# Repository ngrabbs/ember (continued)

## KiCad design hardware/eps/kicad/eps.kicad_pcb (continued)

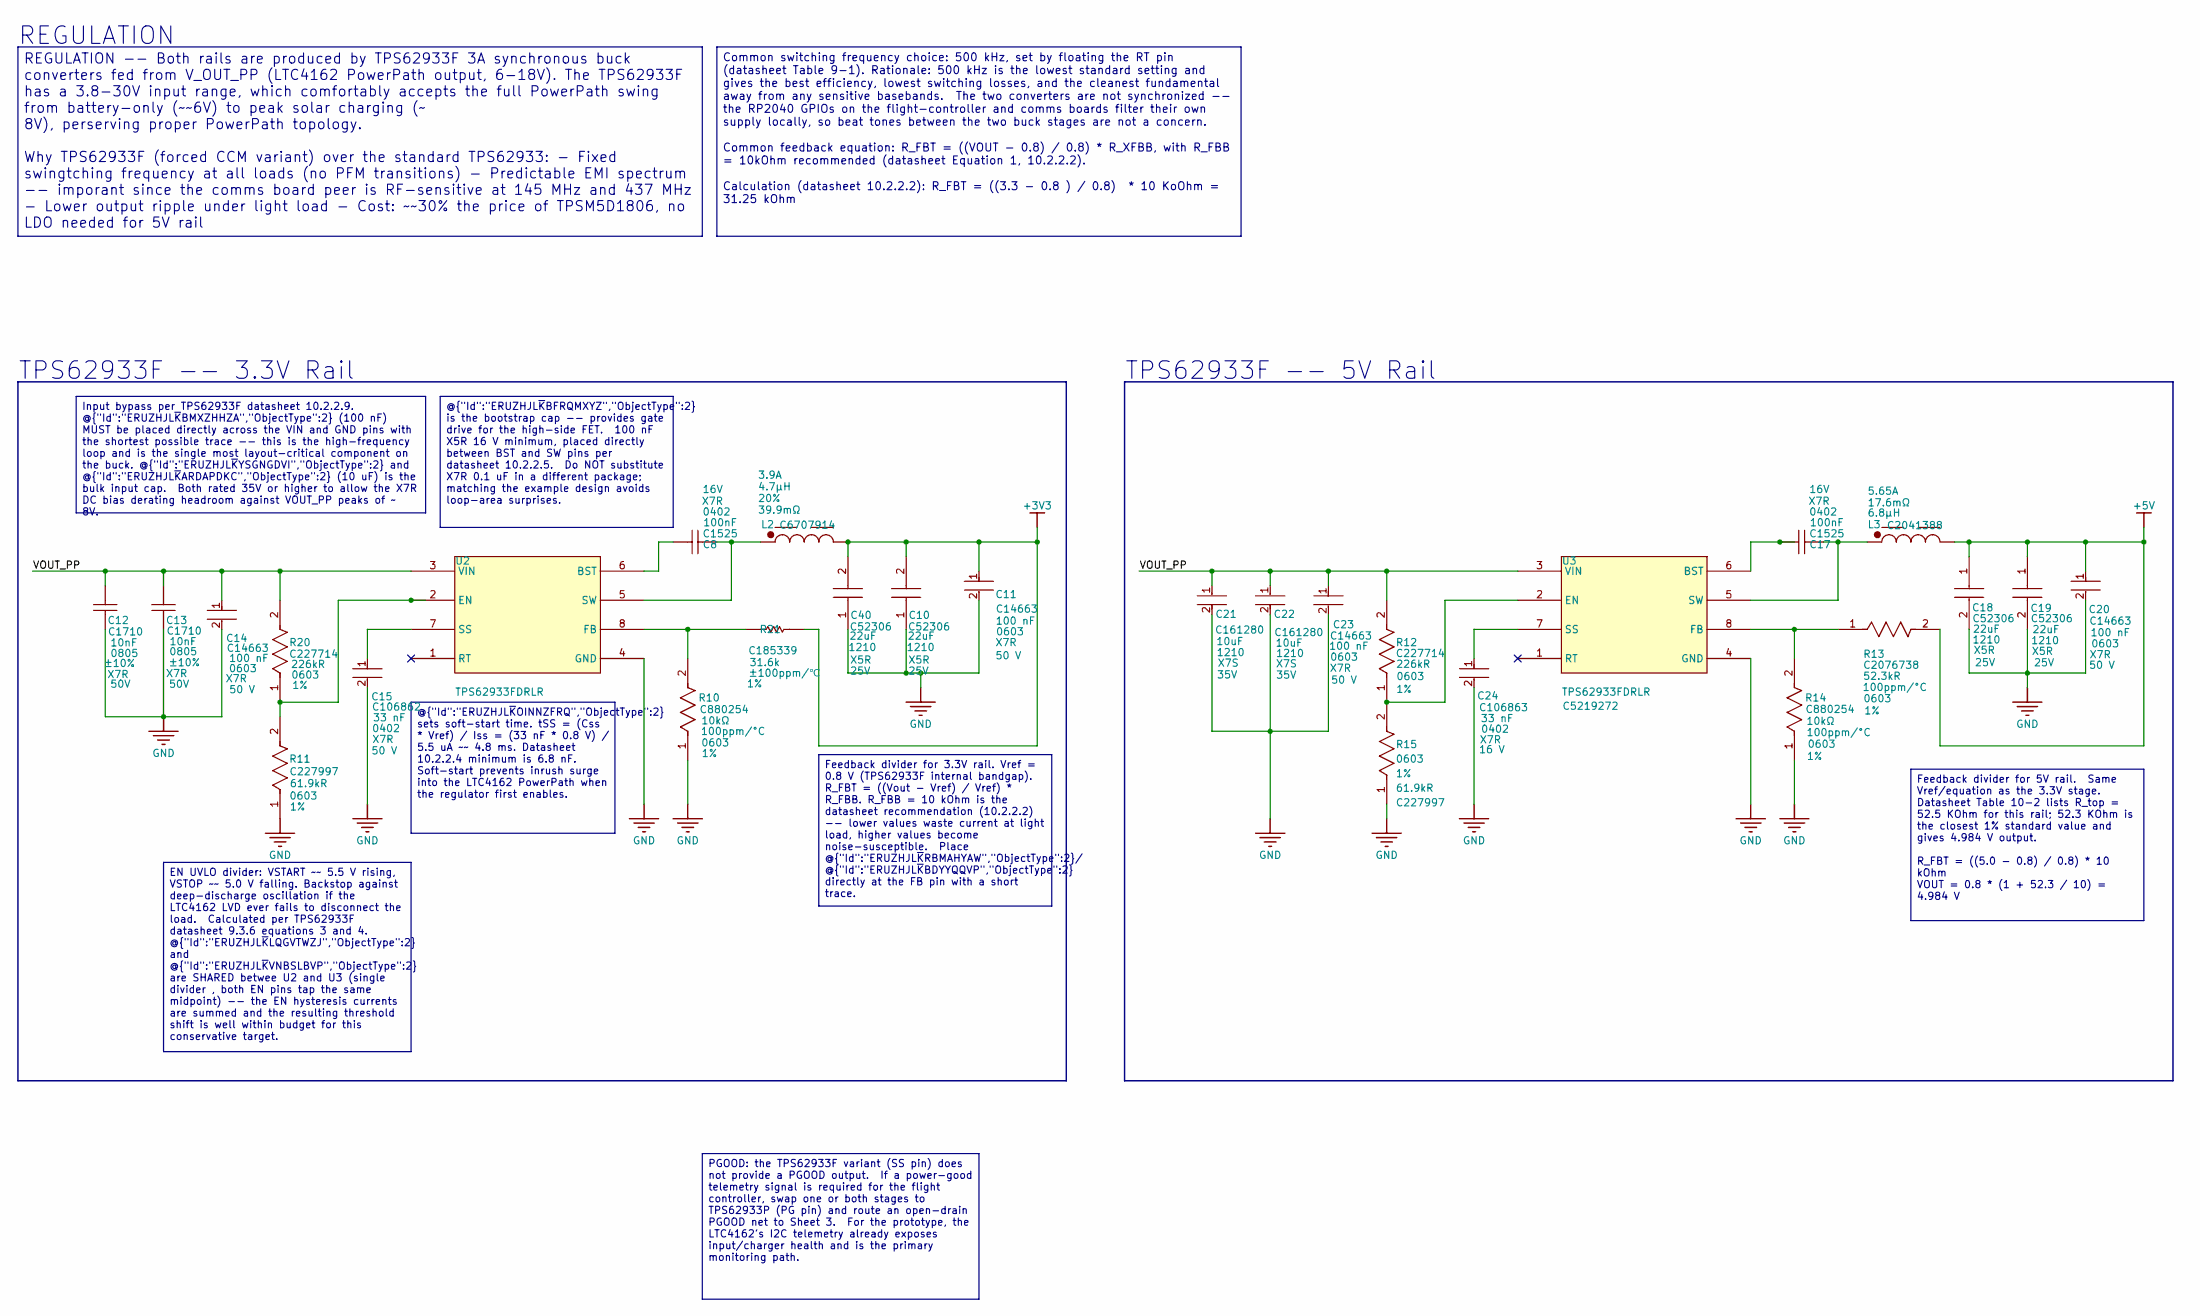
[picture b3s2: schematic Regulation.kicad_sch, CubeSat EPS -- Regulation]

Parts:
C8, C17: CL05B104KO5NNNC; CAPC1050X55X23ML05T13; TOLERANCE (%) ±10%; RATED VOLTAGE 16V; LCSC PART # C1525
C10, C18, C19, C40: CL32A226KAJNNNE; CAPC3225X270N; VOLTAGE 25V; MANUFACTURER_PART_NUMBER CL32A226KAJNNNE; MOUSER PART NUMBER 187-CL32A226KAJNNNE
C11, C14, C20, C23: C14663; FP-CC0603-DA-MFG; VOLTAGE 50 V; VOLTAGE RATING 50 V; MANUFACTURER PART NUMBER CC0603KRX7R9BB104; MOUSER DESCRIPTION Multilayer Ceramic Capacitor, CC Series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
C12, C13: CL21B103KBANNNC; CAPC2013X75X45LL10T25; TOLERANCE (%) ±10%; RATED VOLTAGE 50V; LCSC PART # C1710
C15: CC0402KRX7R9BB333; FP-CC0402-MFG; VOLTAGE RATING 50 V; TOLERANCE 0.1; MANUFACTURER PART NUMBER CC0402KRX7R9BB333; MOUSER DESCRIPTION Cap Ceramic 0.033uF 50VDC X7R 10% SMD 0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
C21, C22: GCM32EC7YA106KA03L; FP-GCM32E-0_3-IPC_B; VOLTAGE RATING (DC) 35V; RATINGS AEC-Q200; LCSC PART # C161280
C24: CC0402KRX7R7BB333; FP-CC0402-MFG; VOLTAGE RATING 16 V; TOLERANCE 0.1; MANUFACTURER PART NUMBER CC0402KRX7R7BB333; DIGIKEY DESCRIPTION CAP CER 0.033UF 16V X7R 0402
L2: 74438357047; WE-MAPI_4030; INDUCTANCE TOLERANCE 20%; CURRENT RATING 3.9A; LCSC PART # C6707914
L3: 74439346068; WE-XHMI_6060; CURRENT RATING 6.5A; INDUCTANCE TOLERANCE 20%; LCSC PART # C2041388
R10, R14: SG73P1JTTD1002F; FP-SG73P1J-MFG; POWER RATING 200mW; VOLTAGE RATING (DC) 50V; LCSC PART # C880254
R11, R15: AC0603FR-0761K9L; FP-AC0603-IPC_C; POWER RATING 100mW; TOLERANCE 1%; LCSC PART # C227997
R12, R20: AC0603FR-07226KL; FP-AC0603-IPC_B; POWER RATING 100mW; VOLTAGE RATING 50V; LCSC PART # C227714
R13: CRCW060352K3FKEA; FP-CRCW0603-e3-IPC_B; VOLTAGE RATING 75V; TOLERANCE 1%; LCSC PART # C2076738
R21: RC0603FR-0731K6L; RESC1608X55X25NL10T15; TOLERANCE 1%; PART NUMBER RC0603FR-0731K6L; LCSC PART # C185339
U2: TPS62933FDRLR; SOT5X3-8_DRL_TEX; MANUFACTURER_PART_NUMBER TPS62933FDRLR
U3: TPS62933FDRLR; SOT5X3-8_DRL_TEX; MANUFACTURER_PART_NUMBER TPS62933FDRLR; LCSC PART # C5219272

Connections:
+3V3: C10.2, C11.1, C40.2, L2.2, R21.2; also elsewhere on the board
+5V: C18.1, C19.1, C20.1, L3.2, R13.2; also elsewhere on the board
/Regulation/VOUT_PP: C12.1, C13.1, C14.1, C21.1, C22.1, C23.1, R12.2, R20.2, U2.3 (VIN), U3.3 (VIN)
GND: C10.1, C11.2, C12.2, C13.2, C14.2, C15.2, C18.2, C19.2, C20.2, C21.2, C22.2, C23.2, C24.2, C40.1, R10.1, R11.1, R14.1, R15.1, U2.4 (GND), U3.4 (GND); also elsewhere on the board
unnamed: C8.1, U2.6 (BST)
unnamed: R11.2, R20.1, U2.2 (EN)
unnamed: R10.2, R21.1, U2.8 (FB)
unnamed: C15.1, U2.7 (SS)
unnamed: C8.2, L2.1, U2.5 (SW)
unnamed: C17.1, U3.6 (BST)
unnamed: R12.1, R15.2, U3.2 (EN)
unnamed: R13.1, R14.2, U3.8 (FB)
unnamed: C24.1, U3.7 (SS)
unnamed: C17.2, L3.1, U3.5 (SW)

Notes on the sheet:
REGULATION
TPS62933F -- 5V Rail
TPS62933F -- 3.3V Rail
Feedback divider for 3.3V rail. Vref = 0.8 V (TPS62933F internal bandgap). R_FBT = ((Vout - Vref) / Vref) * R_FBB. R_FBB = 10 kOhm is the datasheet recommendation (10.2.2.2) -- lower values waste current at light load, higher values become noise-susceptible. Place @{"Id":"ERUZHJL~{K}RBMAHYAW","Obje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
Input bypass per TPS62933F datasheet 10.2.2.9. @{"Id":"ERUZHJL~{K}BMXZHHZA","ObjectType":2} (100 nF) MUST be placed directly across the VIN and GND pins with the shortest possible trace -- this is the high-frequency loop and is the single most layout-critical component on the buck. @{"Id":"ERUZHJL~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
@{"Id":"ERUZHJL~{K}BFRQMXYZ","ObjectType":2} is the bootstrap cap -- provides gate drive for the high-side FET. 100 nF X5R 16 V minimum, placed directly between BST and SW pins per datasheet 10.2.2.5. Do NOT substitute X7R 0.1 uF in a different package; matching the example design avoids loop-area 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
@{"Id":"ERUZHJL~{K}OINNZFRQ","ObjectType":2} sets soft-start time. tSS = (Css * Vref) / Iss = (33 nF * 0.8 V) / 5.5 uA ~~ 4.8 ms. Datasheet 10.2.2.4 minimum is 6.8 nF. Soft-start prevents inrush surge into the LTC4162 PowerPath when the regulator first enables.
EN UVLO divider: VSTART ~~ 5.5 V rising, VSTOP ~~ 5.0 V falling. Backstop against deep-discharge oscillation if the LTC4162 LVD ever fails to disconnect the load. Calculated per TPS62933F datasheet 9.3.6 equations 3 and 4. @{"Id":"ERUZHJL~{K}LQGVTWZJ","ObjectType":2} and @{"Id":"ERUZHJL~{K}VNBSLBVP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
Feedback divider for 5V rail. Same Vref/equation as the 3.3V stage. Datasheet Table 10-2 lists R_top = 52.5 KOhm for this rail; 52.3 KOhm is the closest 1% standard value and gives 4.984 V output. R_FBT = ((5.0 - 0.8) / 0.8) * 10 kOhm VOUT = 0.8 * (1 + 52.3 / 10) = 4.984 V
REGULATION -- Both rails are produced by TPS62933F 3A synchronous buck converters fed from V_OUT_PP (LTC4162 PowerPath output, 6-18V). The TPS62933F has a 3.8-30V input range, which comfortably accepts the full PowerPath swing from battery-only (~~6V) to peak solar charging (~ 8V), perserving prope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
PGOOD: the TPS62933F variant (SS pin) does not provide a PGOOD output. If a power-good telemetry signal is required for the flight controller, swap one or both stages to TPS62933P (PG pin) and route an open-drain PGOOD net to Sheet 3. For the prototype, the LTC4162's I2C telemetry already exposes i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
Common switching frequency choice: 500 kHz, set by floating the RT pin (datasheet Table 9-1). Rationale: 500 kHz is the lowest standard setting and gives the best efficiency, lowest switching losses, and the cleanest fundamental away from any sensitive basebands. The two converters are not synchron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

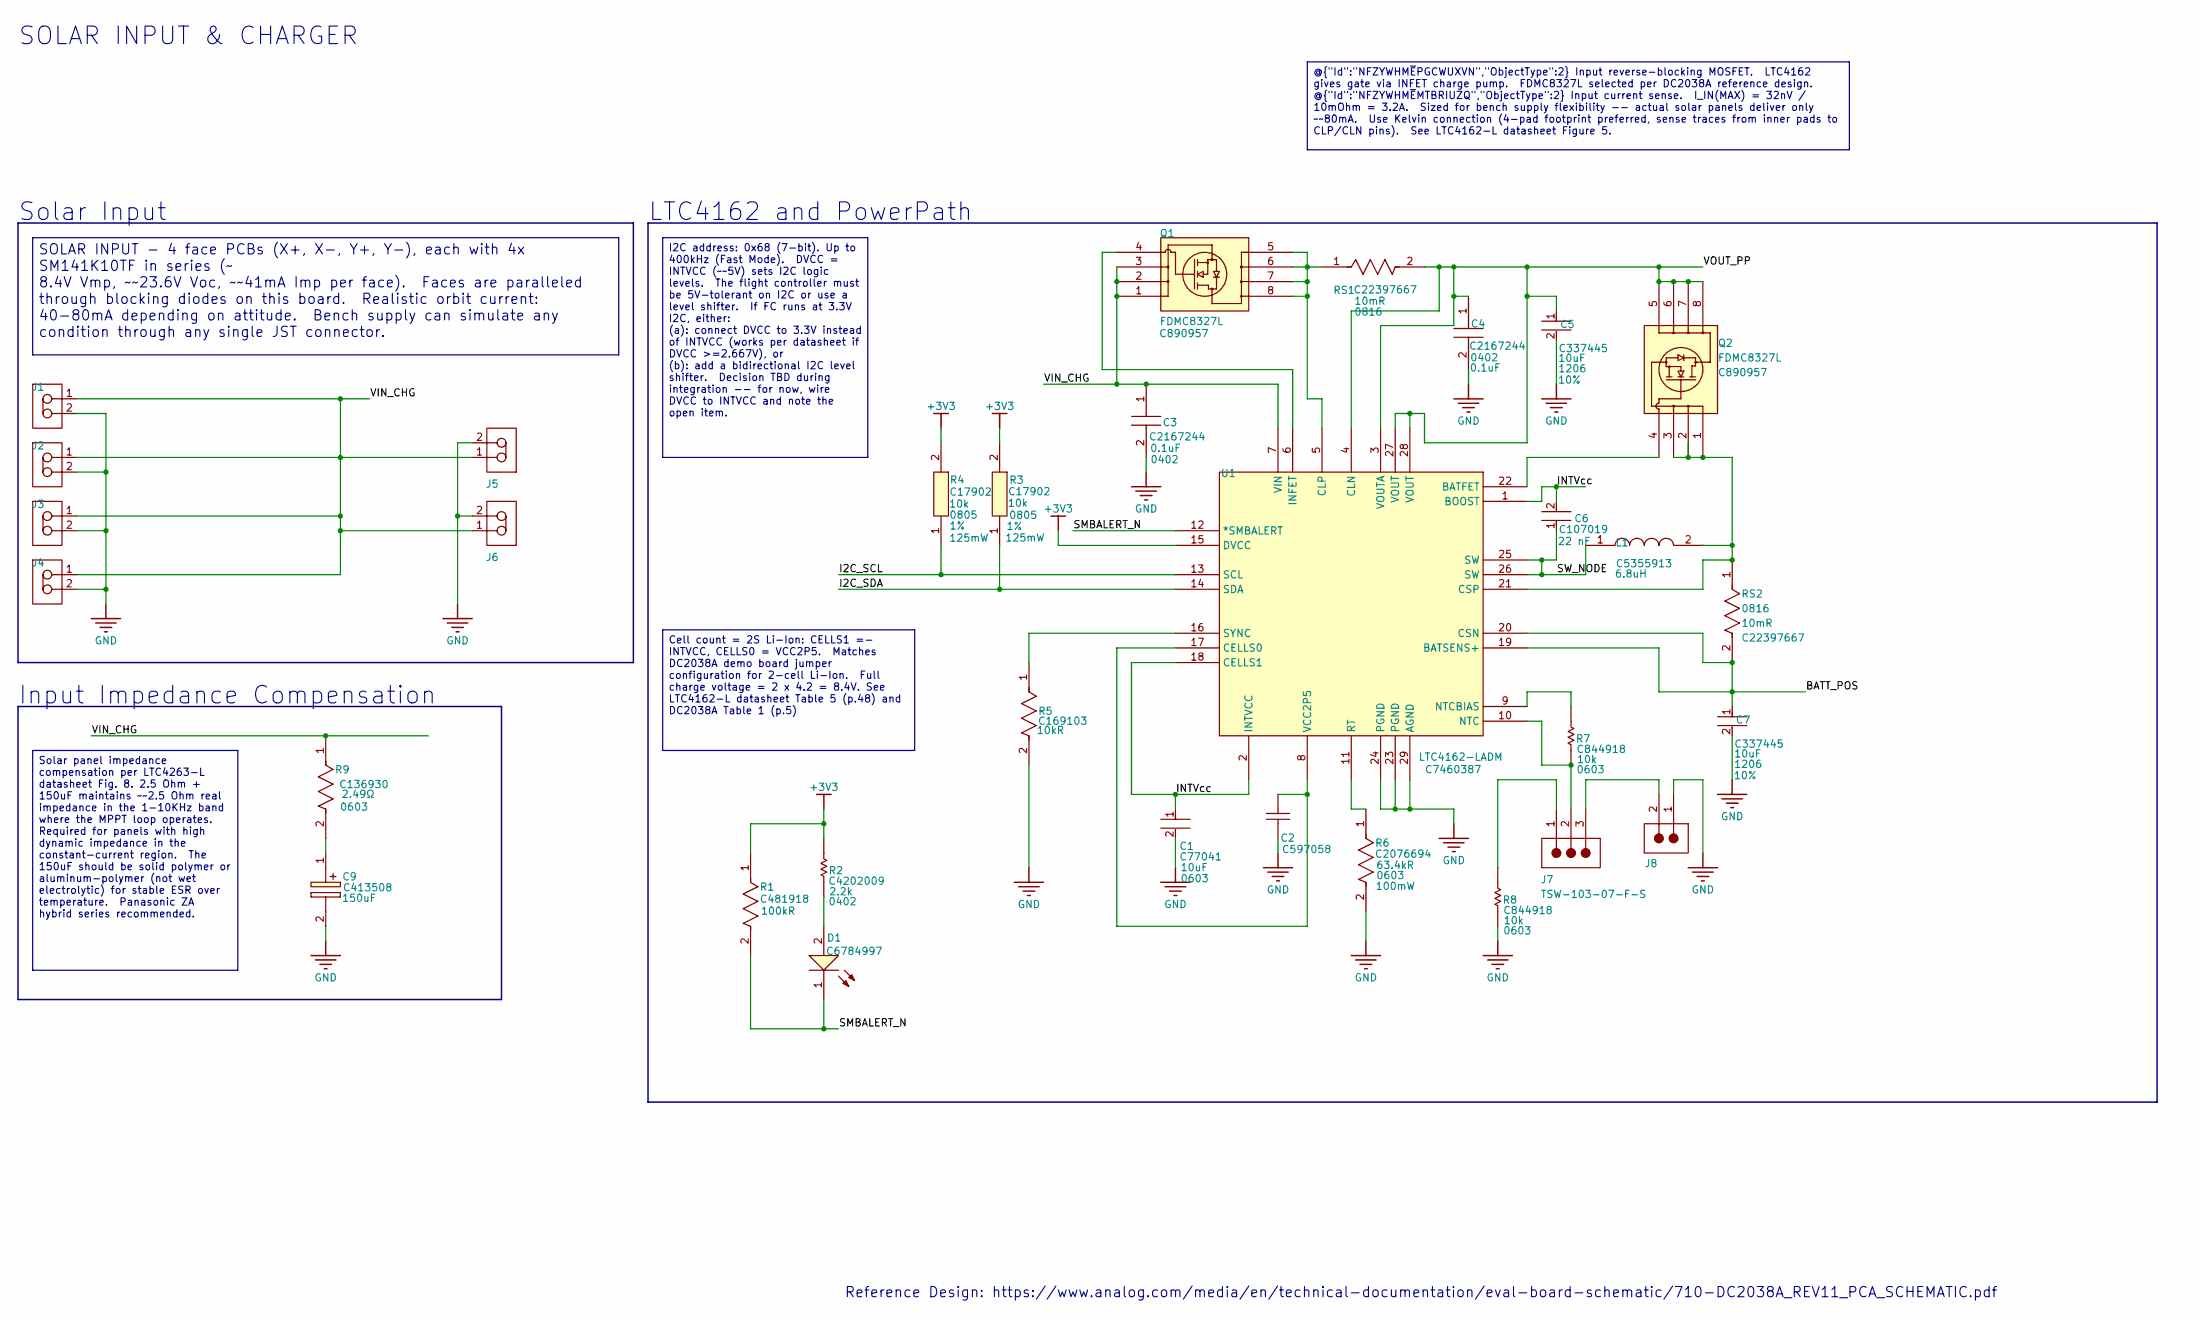
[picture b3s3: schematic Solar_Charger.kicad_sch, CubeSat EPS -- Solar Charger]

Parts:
C1: GRM188R60J106ME47D; FP-GRM188-0_1-e0_2_0_55-IPC_A; VOLTAGE RATING (DC) 6.3V; VOLTAGE RATING 6.3V; LCSC PART # C77041
C2: 0402YD105KAT2A; CAPC1005X56X25ML10T15; PART NUMBER 0402YD105KAT2A; LCSC PART # C597058
C3, C4: 04025C104KAT2A; CAPC1005X56N; MANUFACTURER_PART_NUMBER 04025C104KAT2A; MOUSER PART NUMBER 581-04025C104KAT2A
C5, C7: UMK316BBJ106KL-T; FP-1206-L_3_2_0_3-W_1_6_0-IPC_A; VOLTAGE RATING 50V; TOLERANCE 10%; LCSC PART # C337445
C6: CC0402KRX7R8BB223; FP-CC0402-MFG; VOLTAGE RATING 25 V; TOLERANCE 0.1; MANUFACTURER PART NUMBER CC0402KRX7R8BB223; DIGIKEY DESCRIPTION CAP CER 0.022UF 25V X7R 0402
C9: EEEFK1H151P; EEE0JA152UAP; MANUFACTURER_PART_NUMBER EEEFK1H151P; LCSC PART # C413508
D1: 150060YS75000; WL-SMCW_0603_150060xx75000; REVERSE VOLTAGE 5V; FORWARD VOLTAGE 2V; LCSC PART # C6784997
J1, J2, J3, J4, J5, J6: B2B-PH-K-S(LF)(SN); JST-B2B-PH-K-S_V
J7: TSW-103-07-F-S; SMTC-TSW-103-07-X-S; PARTNUMBER TSW-103-07-F-S
J8: 68000-102HLF; AMPH-68000-102HLF_V; VOLTAGE RATING 1.5kV; FLAMMABILITY RATING UL94V-0
L1: XAL6060-682MEC; XAL6060682MEC; MANUFACTURER_PART_NUMBER XAL6060-682MEC; MOUSER PART NUMBER 994-XAL6060-682MEC
Q1, Q2: FDMC8327L; WDFN8_511DR_OSI; MANUFACTURER_PART_NUMBER FDMC8327L; LCSC PART # C890957
R1: CRCW0402100KFKED; FP-CRCW0402-e3-IPC_C; POWER RATING 63mW; VOLTAGE RATING (DC) 50V; LCSC PART # C481918
R2: CRCW04022K20JNED; RESC1005X40X25NL05T05; PART NUMBER CRCW04022K20JNED; LCSC PART # C4202009
R3, R4: 1206W4F1002T5E; RESC3116X65N; TOLERANCE 1%; MANUFACTURER_PART_NUMBER 1206W4F1002T5E; LCSC PART # C17902
R5: CRCW060310K0JNEA; FP-CRCW0603-e3-MFG; TOLERANCE 5%; VOLTAGE RATING 75V; LCSC PART # C169103
R6: CRCW060363K4FKEA; FP-CRCW0603-e3-IPC_B; VOLTAGE RATING (DC) 75V; VOLTAGE RATING 75V; LCSC PART # C2076694
R7, R8: CRCW060310K0FKEA; RESC1609X50X30NL8T20; VOLTAGE RATING 75 V; LCSC PART # C844918
R9: RT0603FRE072R49L; FP-RT0603-MFG; TOLERANCE 0.01; POWER RATING 0.1W; MANUFACTURER PART NUMBER RT0603FRE072R49L; DIGIKEY DESCRIPTION RES SMD 2.49 OHM 1% 1/10W 0603
RS1, RS2: PRL0816-R010-F-T1; FP-PRL0816-MFG; TOLERANCE 1%; POWER RATING 330mW; LCSC PART # C22397667
U1: LTC4162EUFD-LADMTRPBF; 05-08-1712_ADI; MANUFACTURER_PART_NUMBER LTC4162EUFD-LADM#TRPBF; LCSC PART # C7460387

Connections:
+3V3: R1.1, R2.2, R3.2, R4.2, U1.15 (DVCC); also elsewhere on the board
/Solar_Charger/BATT_POS: C7.1, RS2.2, U1.19 (BATSENS+), U1.20 (CSN)
/Solar_Charger/I2C_SCL: R4.1, U1.13 (SCL)
/Solar_Charger/I2C_SDA: R3.1, U1.14 (SDA)
/Solar_Charger/INTVcc: C1.1, C6.2, U1.1 (BOOST), U1.2 (INTVCC), U1.18 (CELLS1)
/Solar_Charger/SMBALERT_N: D1.1 (K), R1.2, U1.12 (*SMBALERT)
/Solar_Charger/SW_NODE: C6.1, L1.1, U1.25 (SW), U1.26 (SW)
/Solar_Charger/VIN_CHG: C3.1, J1.1, J2.1, J3.1, J4.1, J5.1, J6.1, Q1.1, Q1.2, Q1.3, R9.1, U1.7 (VIN)
/Solar_Charger/VOUT_PP: C4.1, C5.1, Q2.5, Q2.6, Q2.7, Q2.8, RS1.2, U1.3 (VOUTA), U1.4 (CLN), U1.27 (VOUT), U1.28 (VOUT)
GND: C1.2, C2.1, C3.2, C4.2, C5.2, C7.2, C9.2 (-), J1.2, J2.2, J3.2, J4.2, J5.2, J6.2, J8.1, R5.2, R6.2, R8.1, U1.23 (PGND), U1.24 (PGND), U1.29 (AGND); also elsewhere on the board
unnamed: C9.1 (+), R9.2
unnamed: D1.2 (A), R2.1
unnamed: J7.1, R8.2
unnamed: J7.3, J8.2
unnamed: Q2.4, U1.22 (BATFET)
unnamed: C2.2, U1.8 (VCC2P5), U1.17 (CELLS0)
unnamed: Q1.5, Q1.6, Q1.7, Q1.8, RS1.1, U1.5 (CLP)
unnamed: L1.2, Q2.1, Q2.2, Q2.3, RS2.1, U1.21 (CSP)
unnamed: Q1.4, U1.6 (INFET)
unnamed: J7.2, R7.1, U1.10 (NTC)
unnamed: R7.2, U1.9 (NTCBIAS)
unnamed: R6.1, U1.11 (RT)
unnamed: R5.1, U1.16 (SYNC)

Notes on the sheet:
Reference Design: https://www.analog.com/media/en/technical-documentation/eval-board-schematic/710-DC2038A_REV11_PCA_SCHEMATIC.pdf
SOLAR INPUT & CHARGER
Input Impedance Compensation
LTC4162 and PowerPath
Solar Input
SOLAR INPUT - 4 face PCBs (X+, X-, Y+, Y-), each with 4x SM141K10TF in series (~ 8.4V Vmp, ~~23.6V Voc, ~~41mA Imp per face). Faces are paralleled through blocking diodes on this board. Realistic orbit current: 40-80mA depending on attitude. Bench supply can simulate any condition through any singl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
Cell count = 2S Li-Ion: CELLS1 =- INTVCC, CELLS0 = VCC2P5. Matches DC2038A demo board jumper configuration for 2-cell Li-Ion. Full charge voltage = 2 x 4.2 = 8.4V. See LTC4162-L datasheet Table 5 (p.48) and DC2038A Table 1 (p.5)
@{"Id":"NFZYWHM~{E}PGCWUXVN","ObjectType":2} Input reverse-blocking MOSFET. LTC4162 gives gate via INFET charge pump. FDMC8327L selected per DC2038A reference design. @{"Id":"NFZYWHM~{E}MTBRIUZQ","ObjectType":2} Input current sense. I_IN(MAX) = 32nV / 10mOhm = 3.2A. Sized for bench supply flexibili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
Solar panel impedance compensation per LTC4263-L datasheet Fig. 8. 2.5 Ohm + 150uF maintains ~~2.5 Ohm real impedance in the 1-10KHz band where the MPPT loop operates. Required for panels with high dynamic impedance in the constant-current region. The 150uF should be solid polymer or aluminum-polym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
I2C address: 0x68 (7-bit). Up to 400kHz (Fast Mode). DVCC = INTVCC (~~5V) sets I2C logic levels. The flight controller must be 5V-tolerant on I2C or use a level shifter. If FC runs at 3.3V I2C, either: (a): connect DVCC to 3.3V instead of INTVCC (works per datasheet if DVCC >=2.667V), or (b): add a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

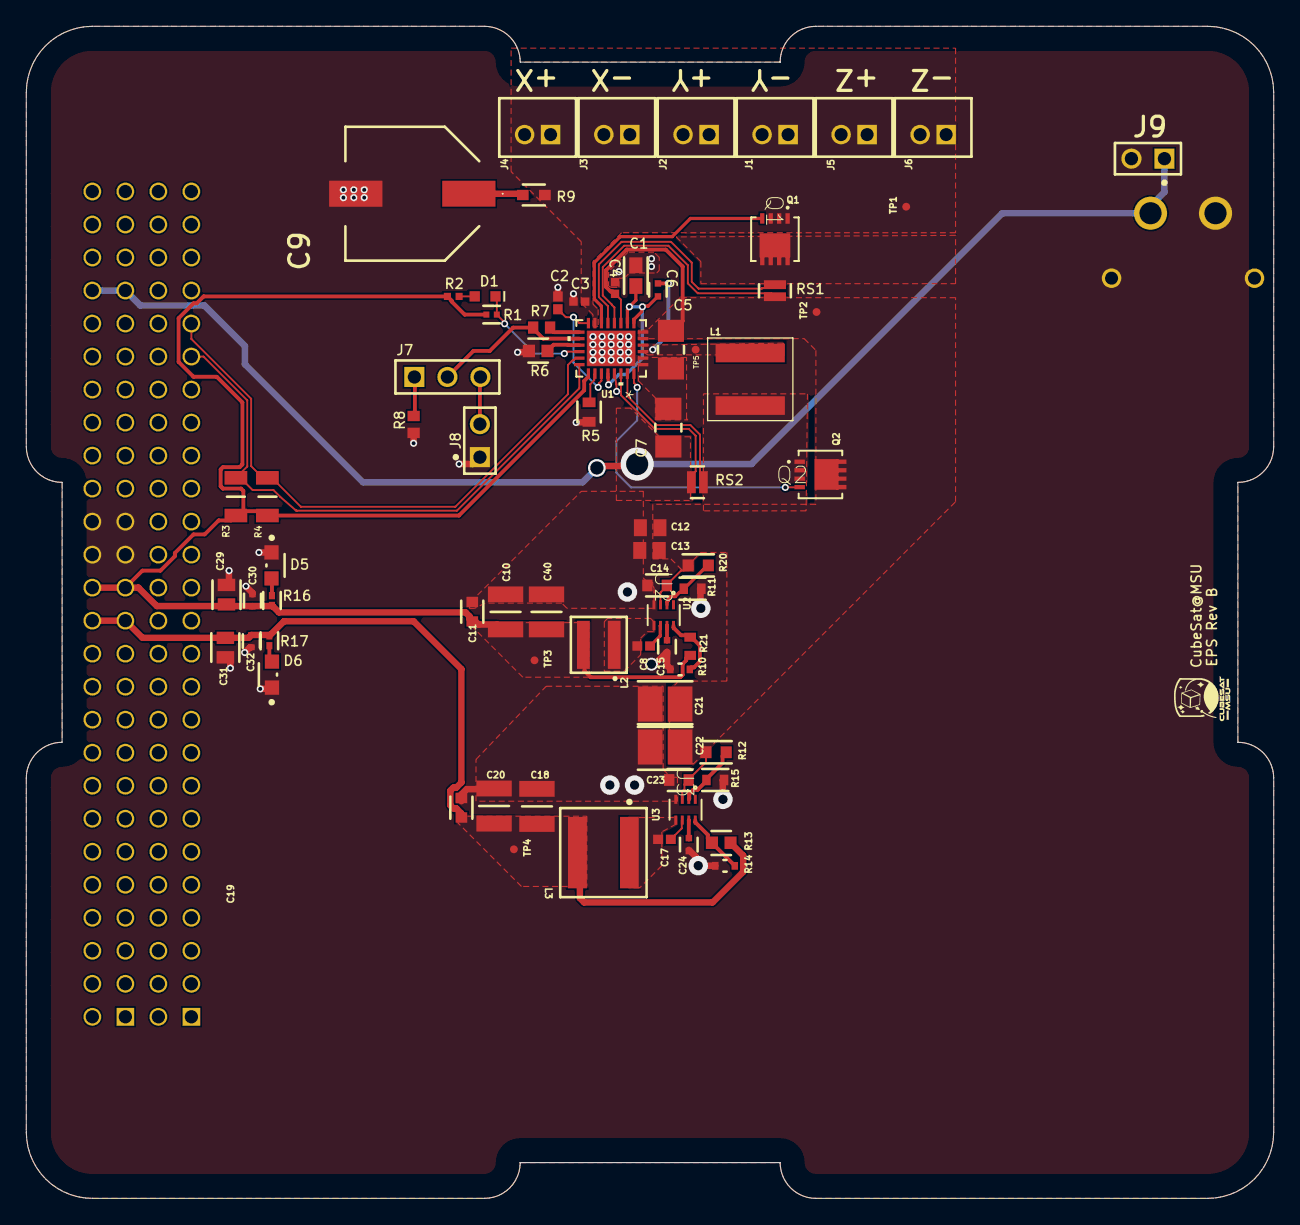
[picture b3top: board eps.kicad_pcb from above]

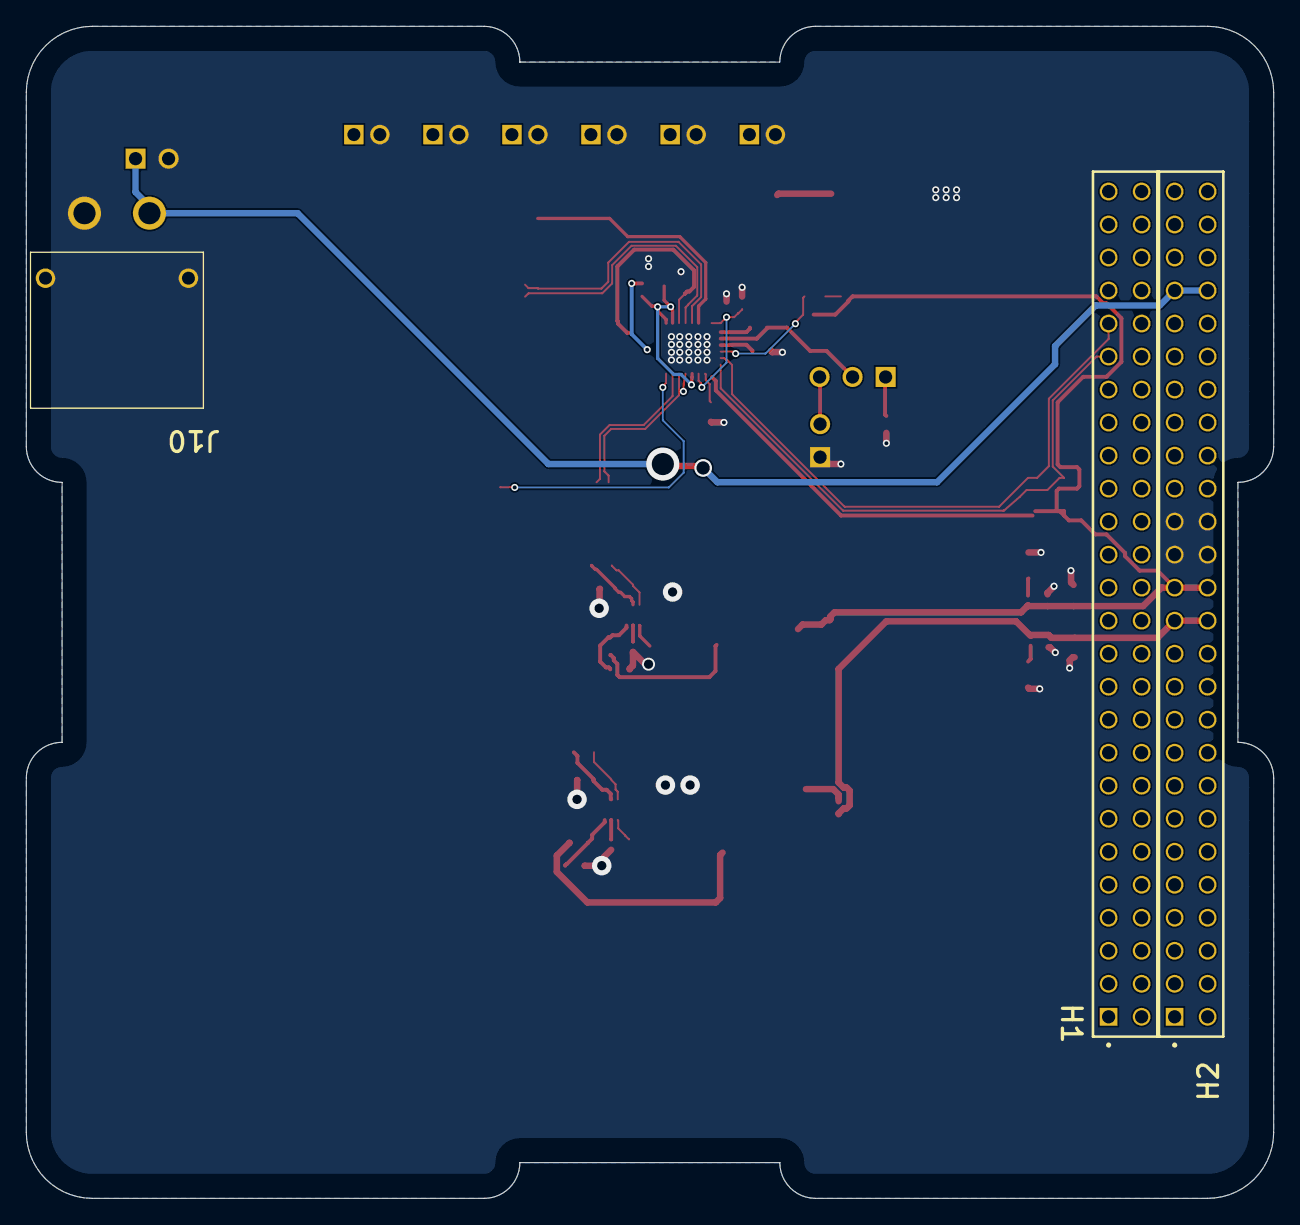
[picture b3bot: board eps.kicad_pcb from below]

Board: 2 copper layers, 96.0 x 90.2 mm, 77 parts (3 on the bottom side), 38 nets.
